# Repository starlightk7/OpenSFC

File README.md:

# OpenSFC

## Introduction

This repository contains OSHW Reproduction Parts related to the Super Famicom (SFC) / Super NES (SNES) game console under the umbrella name OpenSFC. While these parts are primarily developed from the Japanese Super Famicom models, you can build a North American SNES as well as long as you use the appropriate front and rear panels. See the documentation for details.

These parts are freely available under the terms of the [CERN-OHL-S](https://github.com/starlightk7/OpenSFC/blob/main/LICENSE) license for you to use, study, modify, or sell. The source files are provided as-is with no warranty or entitlement for support to you or any users that you sell manufactured boards to. See [LICENSE](https://github.com/starlightk7/OpenSFC/blob/main/LICENSE) and [NOTICE](https://github.com/starlightk7/OpenSFC/blob/main/NOTICE) for details. Please carefully read these files to understand your obligations if you choose to distribute this project or modifications of it.

## Sample Build

<div></div>

## Usage

Suggested usage for the documents and boards in this repository:

* Studying the hardware and learning about it's function
* Aiding repairs and failure diagnostics through the created [schematics](https://starlightk7.github.io/OpenSFC/#/schematic) and boardviews
* Repairing broken consoles via replacement, reproduction boards and tested replacement [BOMs](https://starlightk7.github.io/OpenSFC/#/bom).
* Building a customized console as a DIY project, for hobby or educational purposes.

## Documentation

Please read the [documentation](https://starlightk7.github.io/OpenSFC/) carefully before using the project.

You can also watch SHVC install videos from [1upRestorations (English)](https://youtu.be/3N_iRRNhPbA), [Assistência Retrô (Portuguese)](https://www.youtube.com/watch?v=s9iTc--j23Y), or [Fenris Wolf Retro (English)](https://youtu.be/6wmiuE3He4w?si=xQSYrtJ7eRGYEiC7).

You can watch a controller install video from [1upRestorations (English)](https://www.youtube.com/watch?v=qigm2QdvjLU)

## Getting a Board

The project officially distributes boards from [Japan (inexpensive international shipping available)](https://ko-fi.com/starlightk7/shop), the [US](https://1uprestorations.com/collections/console-mod-parts/products/opensfc-bundle) and the [UK](https://www.retroupgrades.co.uk/product/opensfc-shvc-bundle). If you just wish to simply obtain a board for yourself, it will often be cheaper than ordering from the fab directly.

***Support is offered to those who purchased a board from a vendor listed below. No support is provided for fabricating these files on your own. If you choose that route, you should understand what you are doing and are responsible for ensuring it is done right. I am not responsible for any defects that may arise from improperly manufacturing these files, or for defects arising from modifications made by you or your PCB fab during manufacturing. If you produce these boards for sale without becoming an authorized distributor, you are responsible for any and all customer support related to the product as well as your compliance with the project's license***. 

If you have any questions about this, feel free to contact with questions. If you are interested in becoming an authorized distributor for your region, and thus gaining support for your users, please contact me via Discord or Twitter.

The ultimate goal of this project is to eventually document and reproduce all models, but it will take quite some time. In the meantime, I made the best overall parts (in my opinion) first. If you believe in the long term goal, consider subscribing on Ko-Fi; for the $1 tier you'll also gain access to weekly Dev Logs that teach how boards like these are made. Labor aside, donor boards to research, prototypes, and parts are all expensive, and those funds will help offset those costs to complete more boards.

Feel free to come chat with us on Discord: 

All boards in this project are 28-35 years old at the time of writing. All relevant patents worldwide have long expired. This project is not affiliated with or endorsed by the big N.

## Commissions

I do not have time to build commissions on a regular basis, however, there are members of the retro community whom offer this service.

| US/Canada | EU |
|-----------|----|
| [1upRestorations (United States)'](https://1uprestorations.com/collections/pre-modded-consoles/products/opensfc-custom-build) | [Modding Marius](https://moddingmarius.com/super-nintendo/)

## Disclaimer

**WARNING:** Doing a full build is an advanced project. Please carefully read the documentation and required skills and experience before purchasing or ordering a board. Purchasing boards and parts does not guarantee that you can be successful in doing a build. Significant experience in soldering and desoldering, along with a variety of tools are necessary. Your first build will likely not work on its first boot. Patience, analysis, and debugging will likely be necessary to bring the unit online. Order at your own risk. The author provides no guarantee of your success, and also cannot guarantee that any given vendor can fabricate these boards correctly. If you are ordering boards, please consult with your target vendor before ordering if you wish to order a board.

## Parts Index

### Motherboards

| Part Number | Description | Region | Status| Japan | United States | United Kingdom |
|-------------|-------------|----------------------|-------|-------|---------------|----------------|
| SHVC-CPU-01 (1990) | The original 2-chip motherboard. This board is the best routed motherboard of all two chip models. Early 1/1/1 Units are extremely reliable. Late 2/1/3 units have a high failure rate. | NTSC-U / NTSC-J | Released | [Ko-Fi (Direct)](https://ko-fi.com/starlightk7/shop), [eBay (Direct)](https://www.ebay.com/itm/136746135648), [Etsy (Direct)](https://starlightretro.etsy.com) | [1upRestorations](https://1uprestorations.com/collections/console-mod-parts/products/opensfc-bundle) | [RetroUpgrades](https://www.retroupgrades.co.uk/product/opensfc-shvc-bundle) |
| SNS-CPU-GPM-01 (1991) | Contains the often failing CPU 2A. | NTSC-U / NTSC-J | In Progress | N/A | N/A | N/A |

### Sound Module

| Part Number | Description | Region | Status| Japan | United States | United Kingdom |
|-------------|-------------|----------------------|-------|-------|---------------|----------------|
| TCMK-77XR SHVC-SOUND | The early type, missing resistors on the 2904. Repro for historical purposes only. | NTSC-U / NTSC-J | Planned | N/A | N/A | N/A |
| TCMK-77XR SHVC-SOUND F | This is the late model sound module which fixed missing resistors on the 2904. | NTSC-U / NTSC-J | Released | [Ko-Fi (Direct)](https://ko-fi.com/starlightk7/shop), [eBay (Direct)](https://www.ebay.com/itm/136746135648), [Etsy (Direct)](https://starlightretro.etsy.com) | [1upRestorations](https://1uprestorations.com/collections/console-mod-parts/products/opensfc-bundle) | [RetroUpgrades](https://www.retroupgrades.co.uk/product/opensfc-shvc-bundle) |

### Front Panel Board

| Part Number | Description | Region | Status| Japan | United States | United Kingdom |
|-------------|-------------|----------------------|-------|-------|---------------|----------------|
| TCMK-81X CCK-N10 | Found in SHVC and GPM Super Famicoms | NTSC-J | Released | [Ko-Fi (Direct)](https://ko-fi.com/starlightk7/shop), [eBay (Direct)](https://www.ebay.com/itm/136746135648), [Etsy (Direct)](https://starlightretro.etsy.com)| [1upRestorations](https://1uprestorations.com/collections/console-mod-parts/products/opensfc-bundle) | [RetroUpgrades](https://www.retroupgrades.co.uk/product/opensfc-shvc-bundle) |
| TCMK-81X CCK-N20 | Found in SHVC and GPM North American SNESes | NTSC-U | Released | [Ko-Fi (Direct)](https://ko-fi.com/starlightk7/shop), [eBay(Direct)](https://www.ebay.com/itm/136746135648), [Etsy (Direct)](https://starlightretro.etsy.com) | [1upRestorations](https://1uprestorations.com/collections/console-mod-parts/products/opensfc-bundle) | [RetroUpgrades](https://www.retroupgrades.co.uk/product/opensfc-shvc-bundle) |

### Controllers

| Part Number | Description | Region | Status| Japan | United States | United Kingdom |
|-------------|-------------|----------------------|-------|-------|---------------|----------------|
| 56V313A (1990.6) | Found in 1/1/1 SHVC controllers. 2x shift register model | NTSC-J / NTSC-U | Released | [Ko-Fi (Direct)](https://ko-fi.com/starlightk7/shop), [eBay(Direct)](https://www.ebay.com/itm/137100897247) | [1upRestorations](https://1uprestorations.com/products/opensfc-controllers) | [RetroUpgrades](https://www.retroupgrades.co.uk/) (Coming Soon) |
| 56V313B (1991)   | Found in 2/1/3 SHVC controllers. 1x Obsolete Shift Register, no PAL support | NTSC-J / NTSC-U | Planned | N/A | N/A | N/A |
| 56V313D (1992+)  | Found in controllers for GPM and beyond. 1x Obsolete Shift Register | Universal | Released | [Ko-Fi (Direct)](https://ko-fi.com/starlightk7/shop), [eBay(Direct)](https://www.ebay.com/itm/137100898087) | [1upRestorations](https://1uprestorations.com/products/opensfc-controllers) | [RetroUpgrades](https://www.retroupgrades.co.uk/) (Coming Soon) |
| 56V313A          | L/R Trigger Board | Universal | Released | [Ko-Fi (Direct)](https://ko-fi.com/starlightk7/shop) | [1upRestorations](https://1uprestorations.com/products/opensfc-controllers) | [RetroUpgrades](https://www.retroupgrades.co.uk/) (Coming Soon) |

### Cartridges

There are none currently in progress, but they are planned for future.

### Accessories

There are none currently in progress, but they planned for future.

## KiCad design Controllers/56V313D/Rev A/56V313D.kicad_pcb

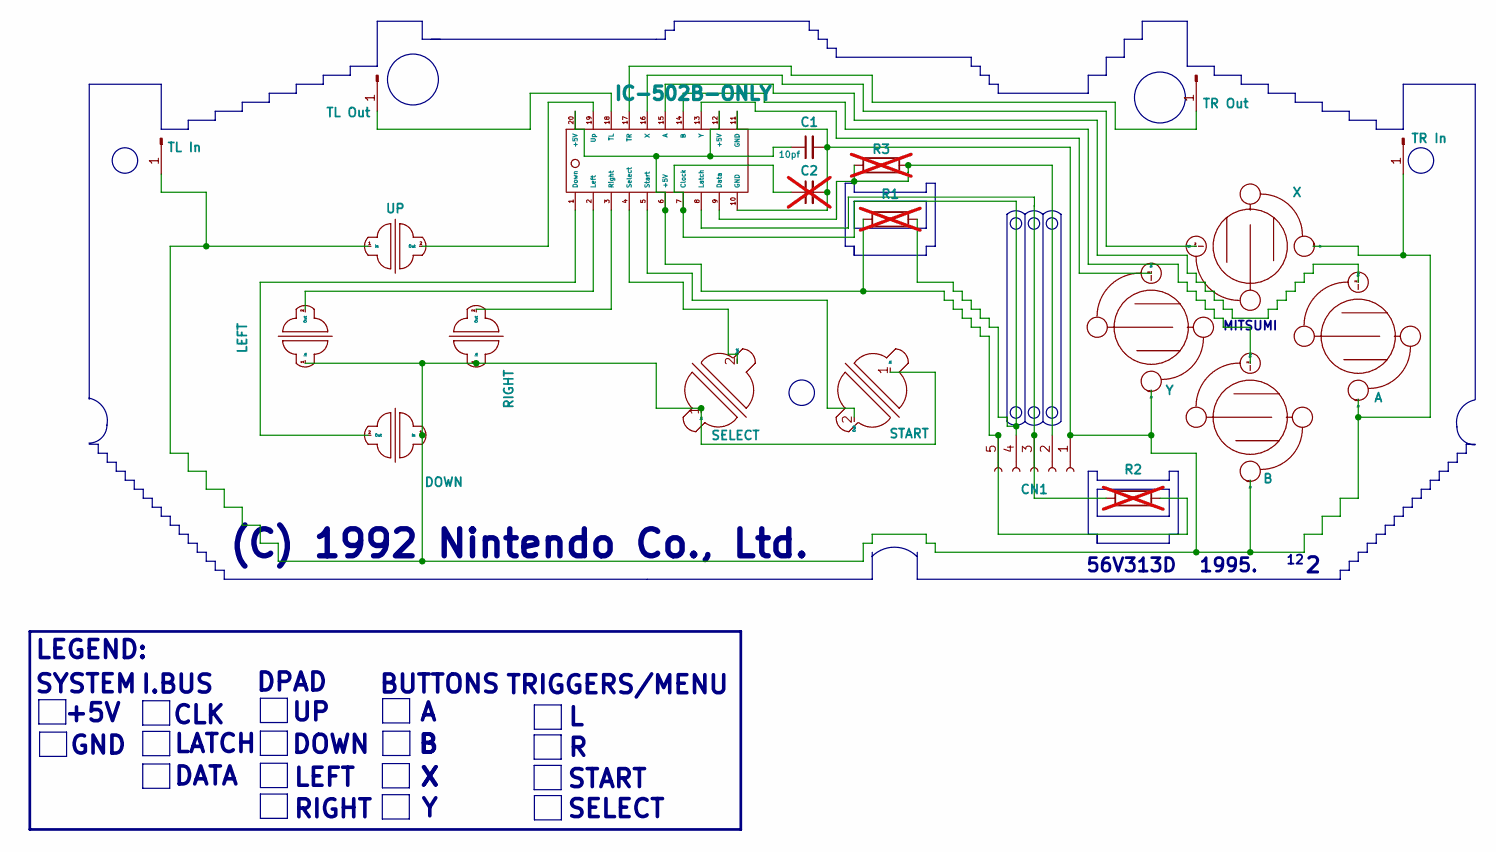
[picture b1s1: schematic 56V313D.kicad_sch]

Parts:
C1: 10pf; C_0805_2012Metric
C2: C_Small; C_0805_2012Metric; not fitted
CN1: Cord Connector; PinHeader_1x05_P2.00mm_Vertical
IC1: IC-502B-ONLY; IC-520B
J1: TR Out; PinHeader_1x01_P2.54mm_Vertical
J2: TR In; PinHeader_1x01_P2.54mm_Vertical
J3: TL In; PinHeader_1x01_P2.54mm_Vertical
J4: TL Out; PinHeader_1x01_P2.54mm_Vertical
R1, R2, R3: R; R_0805_2012Metric; not fitted
S1: LEFT; DPadShoulderButton
S2: SELECT; StartSelectButton
S3: UP; DPadShoulderButton
S4: RIGHT; DPadShoulderButton
S5: DOWN; DPadShoulderButton
S6: START; StartSelectButton
S7: Y; FaceButton
S8: X; FaceButton
S9: B; FaceButton
S10: A; FaceButton

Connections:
unnamed: C1.2, C2.2, CN1.1, IC1.10 (GND), IC1.11 (GND), J2.1, J3.1, S1.1 (In), S2.1 (In), S3.1 (In), S4.1 (In), S5.1 (In), S6.1 (In), S7.1 (In), S8.1 (In), S9.1 (In), S10.1 (In)
unnamed: CN1.2, IC1.9 (Data), R3.1, R3.2
unnamed: CN1.3, IC1.8 (Latch), R2.1
unnamed: C2.1, CN1.4, IC1.7 (Clock), R1.2
unnamed: C1.1, CN1.5, IC1.6 (+5V), IC1.12 (+5V), IC1.20 (+5V), R1.1, R2.2
unnamed: IC1.15 (A), S10.2 (Out)
unnamed: IC1.14 (B), S9.2 (Out)
unnamed: IC1.1 (Down), S5.2 (Out)
unnamed: IC1.2 (Left), S1.2 (Out)
unnamed: IC1.3 (Right), S4.2 (Out)
unnamed: IC1.4 (Select), S2.2 (Out)
unnamed: IC1.5 (Start), S6.2 (Out)
unnamed: IC1.18 (TL), J4.1
unnamed: IC1.17 (TR), J1.1
unnamed: IC1.19 (Up), S3.2 (Out)
unnamed: IC1.16 (X), S8.2 (Out)
unnamed: IC1.13 (Y), S7.2 (Out)

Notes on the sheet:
GND
RIGHT
+5V
LEFT
DOWN
SYSTEM
LATCH
(C) 1992 Nintendo Co., Ltd.
SELECT
START
TRIGGERS/MENU
MITSUMI
LEGEND:
CLK
56V313D
DATA
1995.
BUTTONS
I.BUS
DPAD

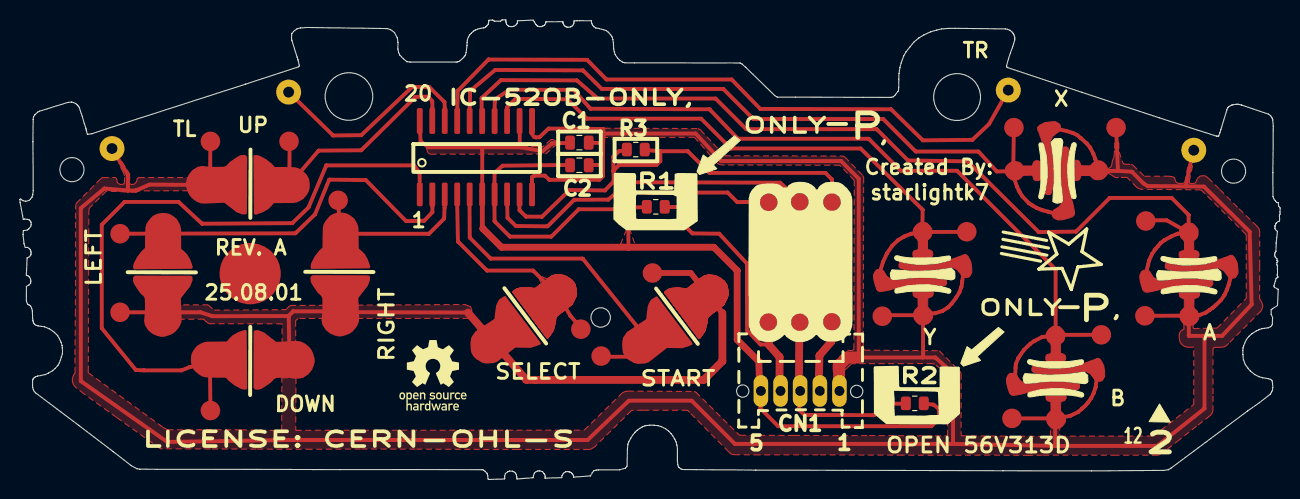
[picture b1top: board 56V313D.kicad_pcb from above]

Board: 2 copper layers, 128.3 x 46.8 mm, 21 parts (0 on the bottom side), 17 nets.

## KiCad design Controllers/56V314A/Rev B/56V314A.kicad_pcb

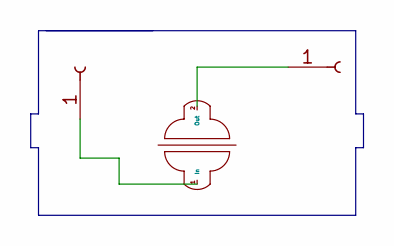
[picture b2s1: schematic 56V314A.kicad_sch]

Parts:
J1, J2: Conn_01x01_Socket; PinHeader_1x01_P2.54mm_Vertical
S1: DPadShoulderButtonV2

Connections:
unnamed: J1.1, S1.1 (In)
unnamed: J2.1, S1.2 (Out)

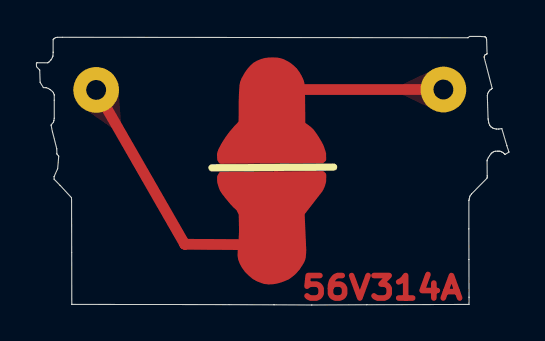
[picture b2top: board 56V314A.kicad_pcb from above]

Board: 2 copper layers, 26.3 x 14.9 mm, 3 parts (0 on the bottom side), 2 nets.

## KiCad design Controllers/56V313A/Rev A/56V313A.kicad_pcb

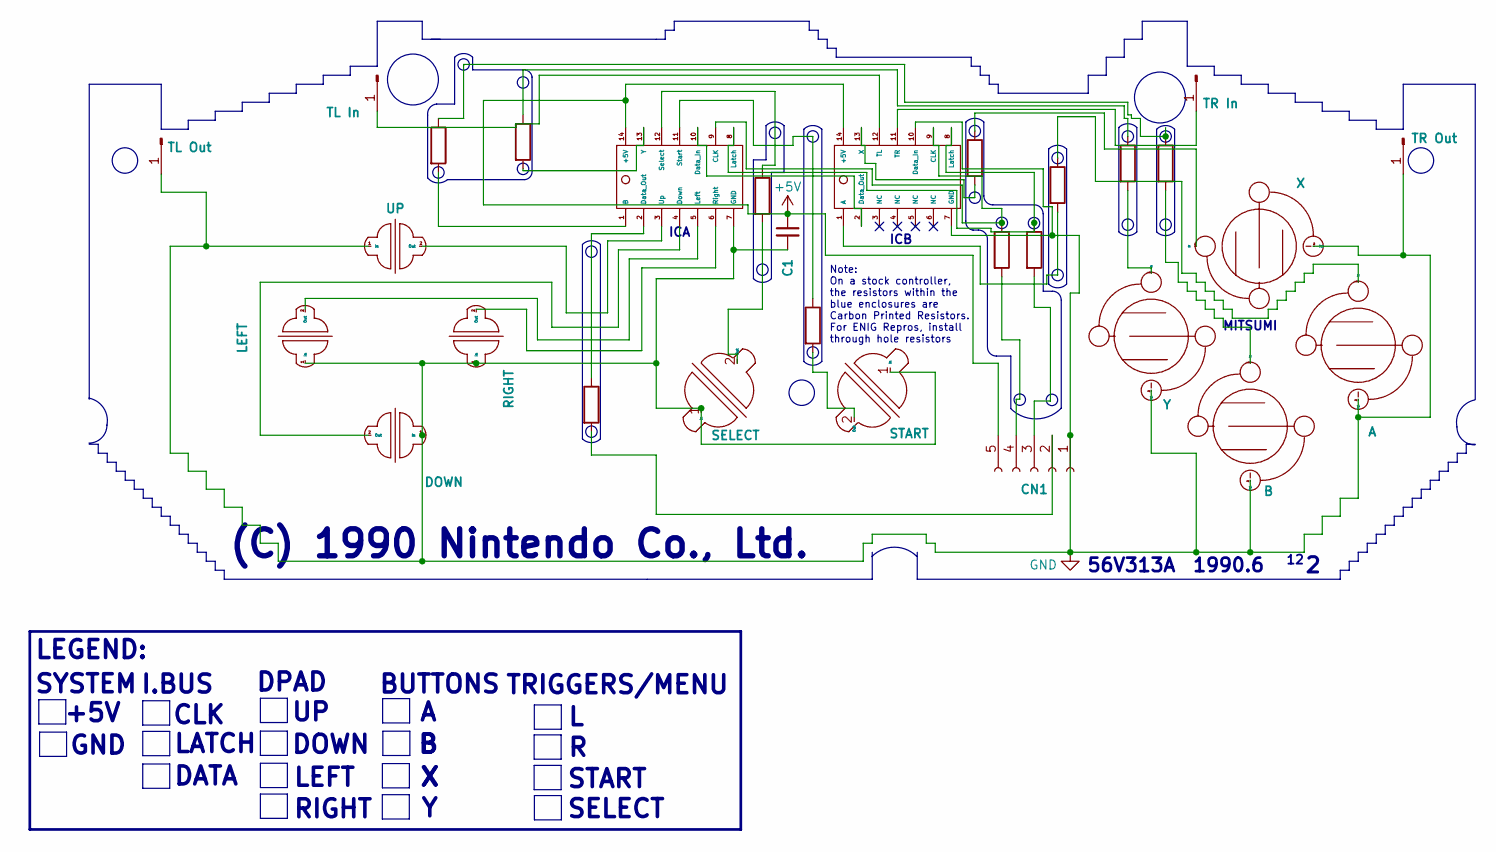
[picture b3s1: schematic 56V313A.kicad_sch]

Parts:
C1: 10pf; C_0805_2012Metric
CN1: Cord Connector; PinHeader_1x05_P2.00mm_Vertical
IC1, IC2: IC_AB
J1: TR In; PinHeader_1x01_P2.54mm_Vertical
J2: TR Out; PinHeader_1x01_P2.54mm_Vertical
J3: TL Out; PinHeader_1x01_P2.54mm_Vertical
J4: TL In; PinHeader_1x01_P2.54mm_Vertical
R1: R; Controller1990_T11
R2: Controller1990_T2
R3: R; Controller1990_T1
R4: R; Controller1990_T3
R5: R; Controller1990_T4
R6: R
R7: R; Controller1990_T6
R8: R; Controller1990_T7
R9: R; Controller1990_T8
R10: R; Controller1990_T9
R11: R; Controller1990_T10
S1: LEFT; DPadShoulderButton
S2: SELECT; StartSelectButton
S3: UP; DPadShoulderButton
S4: RIGHT; DPadShoulderButton
S5: DOWN; DPadShoulderButton
S6: START; StartSelectButton
S7: Y; FaceButtonV2
S8: X; FaceButtonV2
S9: B; FaceButtonV2
S10: A; FaceButtonV2

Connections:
+5V: C1.1, CN1.5, IC1.14 (+5V), IC2.14 (+5V)
GND: C1.2, CN1.1, IC1.7 (GND), IC2.7 (GND), IC2.10 (Data_In), J2.1, J3.1, S1.1 (In), S2.1 (In), S3.1 (In), S4.1 (In), S5.1 (In), S6.1 (In), S7.2 (Out), S8.2 (Out), S9.2 (Out), S10.2 (Out)
unnamed: CN1.2, R1.2
unnamed: CN1.3, R8.2
unnamed: CN1.4, R7.2
unnamed: IC1.1 (B), R3.2
unnamed: IC1.9 (CLK), IC2.9 (CLK), R7.1
unnamed: IC1.10 (Data_In), IC2.2 (Data_Out)
unnamed: IC1.2 (Data_Out), R1.1
unnamed: IC1.4 (Down), S5.2 (Out)
unnamed: IC1.8 (Latch), IC2.8 (Latch), R8.1
unnamed: IC1.5 (Left), S1.2 (Out)
unnamed: IC1.6 (Right), S4.2 (Out)
unnamed: IC1.12 (Select), R4.1
unnamed: IC1.11 (Start), R5.1
unnamed: IC1.3 (Up), S3.2 (Out)
unnamed: IC1.13 (Y), R2.2
unnamed: IC2.1 (A), R9.2
unnamed: IC2.12 (TL), J4.1
unnamed: IC2.11 (TR), J1.1
unnamed: IC2.13 (X), R6.2
unnamed: R2.1, R10.1
unnamed: R3.1, R11.1
unnamed: R4.2, S2.2 (Out)
unnamed: R5.2, S6.2 (Out)
unnamed: R10.2, S7.1 (In)
unnamed: R6.1, S8.1 (In)
unnamed: R11.2, S9.1 (In)
unnamed: R9.1, S10.1 (In)

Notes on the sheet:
GND
RIGHT
+5V
LEFT
ICA
DOWN
Note: On a stock controller, the resistors within the blue enclosures are Carbon Printed Resistors. For ENIG Repros, install through hole resistors
SYSTEM
LATCH
ICB
(C) 1990 Nintendo Co., Ltd.
SELECT
START
TRIGGERS/MENU
MITSUMI
LEGEND:
CLK
56V313A
DATA
1990.6
BUTTONS
I.BUS
DPAD

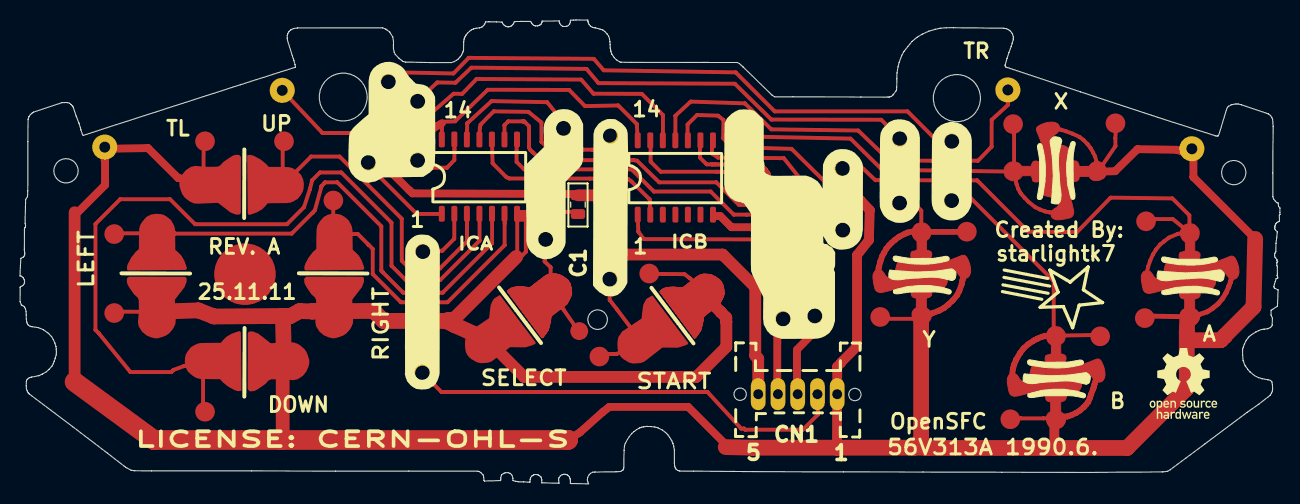
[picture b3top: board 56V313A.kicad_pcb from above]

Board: 2 copper layers, 127.6 x 47.0 mm, 29 parts (0 on the bottom side), 29 nets.

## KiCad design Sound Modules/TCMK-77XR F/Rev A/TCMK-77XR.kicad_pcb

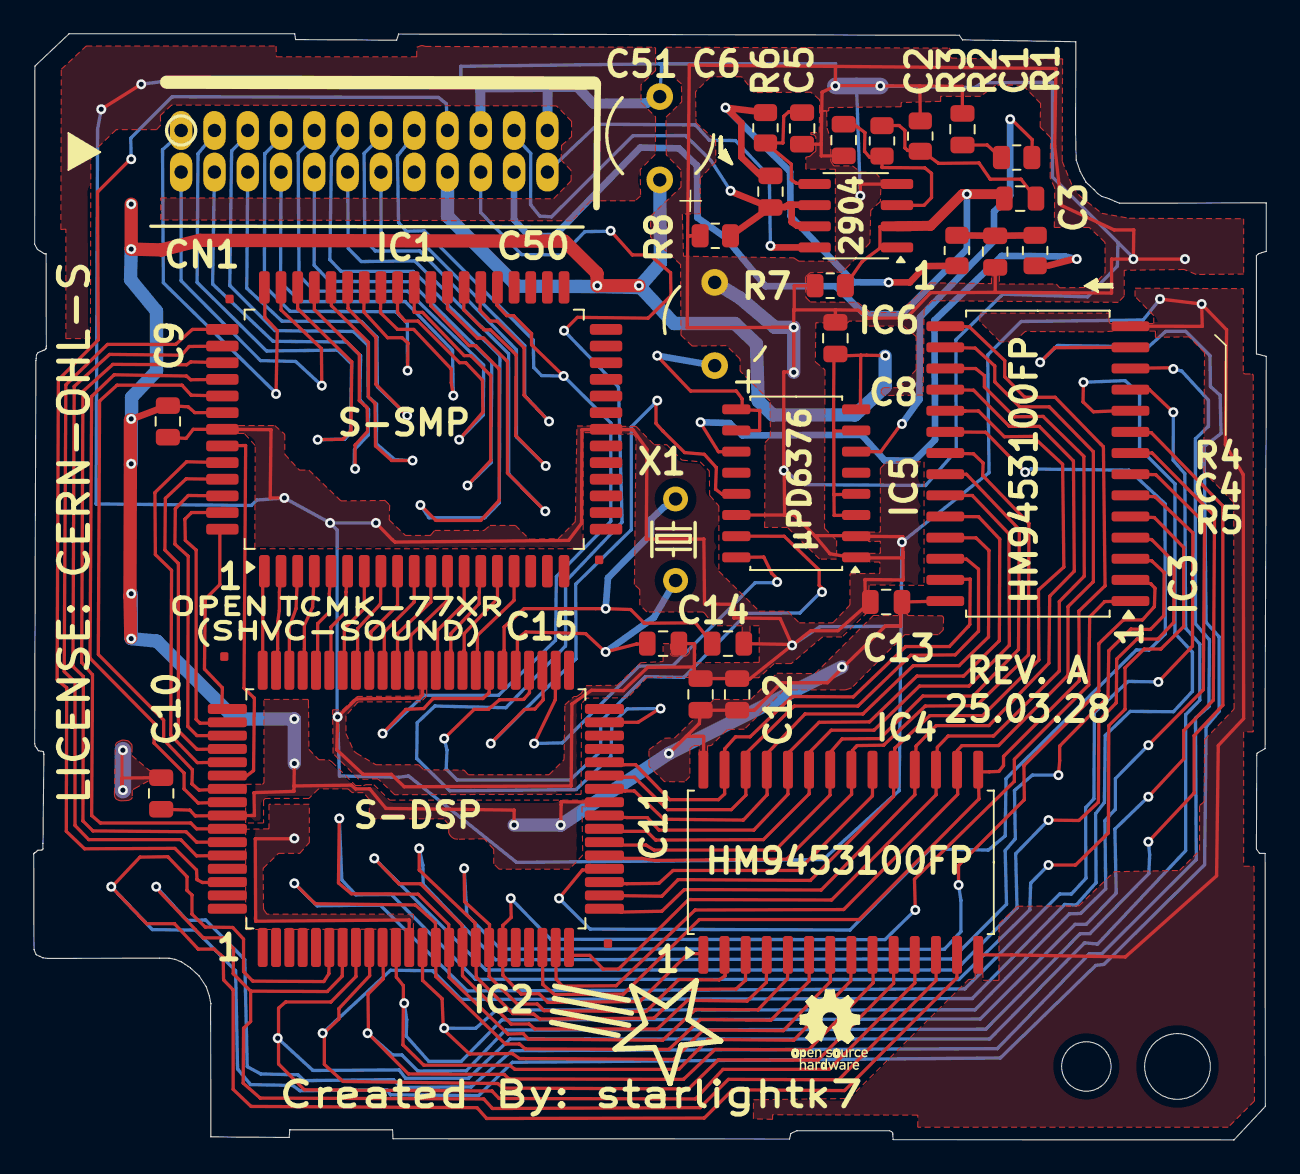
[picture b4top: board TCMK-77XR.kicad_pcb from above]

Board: 2 copper layers, 74.0 x 66.5 mm, 33 parts (1 on the bottom side), 91 nets.

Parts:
C1, C2, C3, C4, C5, C6, C8, C9, C10, C11, C12, C13, C14, C15: C_Small; C_0805_2012Metric
C50, C51: 47µf; C_Radial_D6.3mm_H5.0mm_P2.50mm
CN1: PinHeader_2x12_P2.00mm_Vertical
IC1: S-SMP
IC2: S-DSP
IC3, IC4: SOP-28_8.4x18.16mm_P1.27mm
IC5: SOIC-16W_5.3x10.2mm_P1.27mm
IC6: SOIC-8_3.9x4.9mm_P1.27mm
R1, R2, R3, R4, R5, R6: 22k; R_0805_2012Metric
R7, R8: 5.1k; R_0805_2012Metric
U99: NCStub
X1: 24.576Mhz; Crystal_HC18-U_Vertical

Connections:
+5V: C8.2, C9.1, C10.2, C11.1, C12.1, C13.1, C51.1, CN1.18 (+5V), IC1.57 (+5V), IC2.33 (+5V), IC2.73 (+5V), IC3.28 (VCC), IC4.28 (VCC), IC5.3 (NC), IC5.4 (DVDD), IC5.7 (AVDD), IC5.8 (AVDD)
A0: IC2.9 (DSP_RAM_A0), IC3.10 (A0), IC4.10 (A0)
A1: IC2.10 (DSP_RAM_A1), IC3.9 (A1), IC4.9 (A1)
A2: IC2.11 (DSP_RAM_A2), IC3.8 (A2), IC4.8 (A2)
A3: IC2.13 (DSP_RAM_A3), IC3.7 (A3), IC4.7 (A3)
A4: IC2.14 (DSP_RAM_A4), IC3.6 (A4), IC4.6 (A4)
A5: IC2.15 (DSP_RAM_A5), IC3.5 (A5), IC4.5 (A5)
A6: IC2.16 (DSP_RAM_A6), IC3.4 (A6), IC4.4 (A6)
A7: IC2.17 (DSP_RAM_A7), IC3.3 (A7), IC4.3 (A7)
A12: IC2.18 (DSP_RAM_A12), IC3.2 (A12), IC4.2 (A12)
A14: IC2.19 (DSP_RAM_A14), IC3.1 (A14), IC4.1 (A14)
AVCC: CN1.24 (AVCC), IC6.8 (V+)
BCLK: IC2.42 (DAC_BCLK), IC5.16 (CLK)
CE0: IC2.28 (DSP_RAM_/CE0), IC3.20 (/CE)
CPU0: CN1.7 (CPU_D0), IC1.45 (CPU_D0)
CPU1: CN1.8 (CPU_D1), IC1.44 (CPU_D1)
CPU2: CN1.9 (CPU_D2), IC1.43 (CPU_D2)
CPU3: CN1.10 (CPU_D3), IC1.42 (CPU_D3)
CPU4: CN1.11 (CPU_D4), IC1.41 (CPU_D4)
CPU5: CN1.12 (CPU_D5), IC1.40 (CPU_D5)
CPU6: CN1.13 (CPU_D6), IC1.39 (CPU_D6)
CPU7: CN1.14 (CPU_D7), IC1.38 (CPU_D7)
D0: IC2.8 (DSP_RAM_D0), IC3.11 (D0), IC4.11 (D0)
D1: IC2.7 (DSP_RAM_D1), IC3.12 (D1), IC4.12 (D1)
D2: IC2.6 (DSP_RAM_D2), IC3.13 (D2), IC4.13 (D2)
DAC: IC2.44 (DAC_DATA), IC5.15 (SI/LSI)
DCK: CN1.17 (DCK), IC2.78 (DCK)
GND: C1.1, C2.1, C4.2, C5.1, C8.1, C9.2, C10.1, C11.2, C12.2, C13.2, C14.2, C15.2, C50.2, C51.2, CN1.19 (GND), CN1.23 (GND), IC1.26 (GND), IC1.58 (GND), IC2.12 (GND), IC2.52 (GND), IC3.14 (GND), IC4.14 (GND), IC5.1 (4/8_f_S_SEL), IC5.2 (D.GND), IC5.14 (LRSEL/RSI), IC6.4 (V-), R2.1, R7.1, R8.1
IN2: C6.2, R4.1, R6.1
L: C6.1, CN1.21 (AUDIO-L), IC6.6 (II2), IC6.7 (OUT2), R8.2
L.OUT: IC5.11 (L.OUT), R5.1
LRCK: IC2.43 (DAC_LRCK), IC5.13 (LRCK/WDCK)
MUTE: CN1.20 (/MUTE), IC2.39 (/MUTE)
unnamed: C1.2, R1.1
unnamed: C3.1, R2.2, R3.1
unnamed: C4.1, R4.2, R5.2
unnamed: CN1.16 (NC), U99.1 (NC)
unnamed: IC1.5 (SMP_A0), IC2.60 (SMP_A0)
unnamed: IC1.4 (SMP_A1), IC2.61 (SMP_A1)
unnamed: IC1.3 (SMP_A2), IC2.62 (SMP_A2)
unnamed: IC1.2 (SMP_A3), IC2.63 (SMP_A3)
unnamed: IC1.1 (SMP_A4), IC2.64 (SMP_A4)
unnamed: IC1.64 (SMP_A5), IC2.65 (SMP_A5)
unnamed: IC1.63 (SMP_A6), IC2.66 (SMP_A6)
unnamed: IC1.62 (SMP_A7), IC2.67 (SMP_A7)
unnamed: IC1.61 (SMP_A8), IC2.68 (SMP_A8)
unnamed: IC1.60 (SMP_A9), IC2.69 (SMP_A9)
unnamed: IC1.59 (SMP_A10), IC2.70 (SMP_A10)
unnamed: IC1.56 (SMP_A11), IC2.71 (SMP_A11)
unnamed: IC1.55 (SMP_A12), IC2.72 (SMP_A12)
unnamed: IC1.54 (SMP_A13), IC2.74 (SMP_A13)
unnamed: IC1.53 (SMP_A14), IC2.75 (SMP_A14)
unnamed: IC1.52 (SMP_A15), IC2.76 (A15)
unnamed: IC1.16 (SMP_CLK), IC2.48 (SMP_CLK)
unnamed: IC1.14 (SMP_CLKEN), IC2.50 (SMP_CLKEN)
unnamed: IC1.13 (SMP_D0), IC2.51 (SMP_D0)
unnamed: IC1.12 (SMP_D1), IC2.53 (SMP_D1)
unnamed: IC1.11 (SMP_D2), IC2.54 (SMP_D2)
unnamed: IC1.10 (SMP_D3), IC2.55 (SMP_D3)
unnamed: IC1.9 (SMP_D4), IC2.56 (SMP_D4)
unnamed: IC1.8 (SMP_D5), IC2.57 (SMP_D5)
unnamed: IC1.7 (SMP_D6), IC2.58 (SMP_D6)
unnamed: IC1.6 (SMP_D7), IC2.59 (SMP_D7)
unnamed: IC1.15 (SMP_R/W), IC2.49 (SMP_R/W)
unnamed: IC2.34 (DSP_RAM_A8), IC3.25 (A8), IC4.25 (A8)
unnamed: IC2.32 (DSP_RAM_A9), IC3.24 (A9), IC4.24 (A9)
unnamed: IC2.29 (DSP_RAM_A10), IC3.21 (A10), IC4.21 (A10)
unnamed: IC2.31 (DSP_RAM_A11), IC3.23 (A11), IC4.23 (A11)
unnamed: IC2.35 (DSP_RAM_A13), IC3.26 (A13), IC4.26 (A13)
unnamed: IC2.22 (DSP_RAM_D3), IC3.15 (D3), IC4.15 (D3)
unnamed: IC2.23 (DSP_RAM_D4), IC3.16 (D4), IC4.16 (D4)
unnamed: IC2.24 (DSP_RAM_D5), IC3.17 (D5), IC4.17 (D5)
unnamed: IC2.25 (DSP_RAM_D6), IC3.18 (D6), IC4.18 (D6)
unnamed: IC2.26 (DSP_RAM_D7), IC3.19 (D7), IC4.19 (D7)
unnamed: IC2.27 (DSP_RAM_/CE1), IC4.20 (/CE)
unnamed: IC2.30 (DSP_RAM_/OE), IC3.22 (/OE), IC4.22 (/OE)
unnamed: IC2.36 (DSP_RAM_/WE), IC3.27 (/WE), IC4.27 (/WE)
unnamed: C50.1, IC5.9 (R.REF), IC5.10 (L.REF)
unnamed: C2.2, IC6.3 (IN1), R3.2
unnamed: C5.2, IC6.5 (IN2), R6.2
PA0: CN1.3 (PA0), IC1.49 (PA0)
PA1: CN1.4 (PA1), IC1.48 (PA1)
PA6: CN1.2 (PA6), IC1.50 (PA6_(CS))
PA7: CN1.1 (PA7), IC1.51 (PA7_(/CS))
PRD: CN1.6 (/PRD), IC1.46 (/PRD)
PWR: CN1.5 (/PWR), IC1.47 (/PWR)
R: C3.2, CN1.22 (AUDIO-R), IC6.1 (OUT1), IC6.2 (II1), R7.2
R.OUT: IC5.6 (R.OUT), R1.2
RST: CN1.15 (/RESET), IC1.37 (/RESET), IC2.47 (/RESET)
X.IN: C14.1, IC2.46 (XTAL_IN), X1.2
X.OUT: C15.1, IC2.45 (XTAL_OUT), X1.1

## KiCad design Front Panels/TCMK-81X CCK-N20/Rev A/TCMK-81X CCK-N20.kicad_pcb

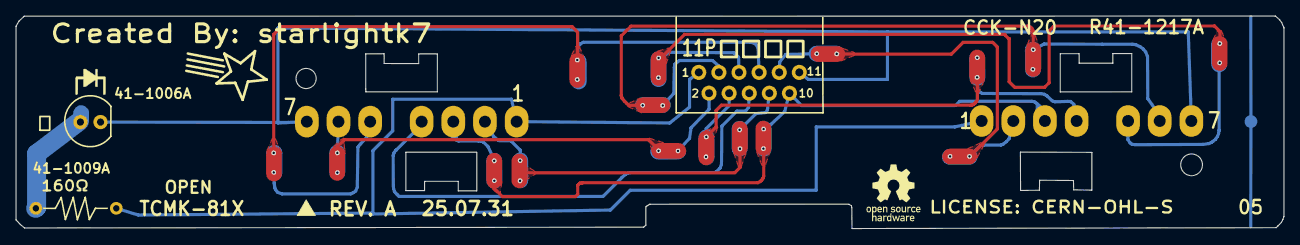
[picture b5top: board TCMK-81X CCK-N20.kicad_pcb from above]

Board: 2 copper layers, 160.2 x 26.8 mm, 5 parts (0 on the bottom side), 12 nets.

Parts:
D1: LED; LED_D1.8mm_W1.8mm_H2.4mm_Horizontal_O6.35mm_Z1.6mm
R1: 160Ω; R_Axial_DIN0207_L6.3mm_D2.5mm_P10.16mm_Horizontal
U1: 11 Pin FFC Connector; ControllerRibbon
U2, U3: Controller Port; ControllerPort

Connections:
2: U1.2, U3.6 (IOBIT)
3: U1.3, U2.6 (IOBIT)
4: U1.4, U2.4 (D1)
5: U1.5, U2.5 (D2)
8: U1.8, U3.2 (CLK)
9: U1.9, U2.2 (CLK)
10: U1.10, U2.3 (LAT), U3.3 (LAT)
GND: D1.1 (K), U1.11, U2.7 (GND), U3.7 (GND)
L+: D1.2 (A), R1.2
unnamed: U1.6, U3.4 (D1)
unnamed: U1.7, U3.5 (D2)
R: R1.1, U1.1, U2.1 (+5V), U3.1 (+5V)

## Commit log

2025-10-10 Initial Relase of Documentation
2025-10-10 Initial Release of OpenSFC
    This commit provides the initial release of the OpenSFC Project.
    The SHVC-CPU-01 board along with it's SHVC-SOUND module, and
    both the SFC and SNES style Front Panel Controller Port Boards
    are reproduced, tested, and fully working with no known bugs as
    of the time of writing.
2025-10-10 Fix Vendor Links
2025-10-10 No longer a placeholder
2025-10-13 Clarify README
2025-10-27 Migrate BOM to Google Docs, Fix C82
    For some reason C82 was no on the spreadsheet even though its on
    the iBOM and Schematic. I fixed that (12nF) and also migrated the
    bom to Google Docs for easier accessibility and maintenance.
2025-10-27 Release SHVC-CPU-01 Rev A SP1 Back Schematic
    Fixes transistor symbols which were visually inaccurate, though
    wired correctly.
    Thanks to RGBeter for reporting this issue.
2025-10-30 Release SHVC-CPU-01 Rev A SP2 Back Schematic
    Also corrects visual inaccuracy in the audio transistors.
2025-12-01 Add Assistência Retrô's Video
    Great video created for our users from Brazil. Many thanks!
2025-12-01 Add Modding Marius to list of commission providers.
2025-12-01 Correct video formatting
2025-12-21 Add Fenris Wolf Retro video
2026-02-23 Add docs for controller, update for nav groups, fix bugs
2026-02-23 Fix Back Image
2026-02-23 Fix Controller Schematic Links
2026-02-23 Fix typo
2026-02-23 Fix more typos
2026-03-06 Add Cache Busting
2026-03-06 Release OpenSFC Controllers: 1990 and 1992 Models
    Initial release.
2026-03-24 Fix schema note for Audio Balance Mod
    Noted the wrong pin to attach the cap to on the schematic diagram
    comments.
    I apologize for the mistake and thanks to /u/Yekomhxc for reporting
    There was no mistake on the actual board itself.
2026-03-24 Fix note on Audio Balance Fix

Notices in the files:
Controllers/56V313A/Rev A/56V313A.kicad_pcb:
LICENSE: CERN-OHL-S
